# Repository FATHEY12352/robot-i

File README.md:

<div align="center">

<!-- Replace the image path below with your actual product photo in assets/hero_arm.png -->

# 🦾 Robot-i | SO-101 Embodied AI Robotic Arm

**Commercial-Grade, Plug-and-Play 6-DOF Imitation Learning Manipulator & Desktop Control Suite**

[Overview](#-overview) • [Live Demo](#-autonomous-ai-in-action) • [Hardware Specs](#-hardware-specifications) • [Quick Start](#-out-of-the-box-quick-start) • [Architecture](#-system-architecture) • [Versions](#-repository-structure)

</div>

---

## 🌟 Overview

The **Robot-i SO-101** is a complete, ready-to-deploy **6-DOF Embodied AI Robotic Arm** engineered for research labs, industrial automation prototyping, universities, and robotics developers.

Instead of writing rigid, hardcoded inverse-kinematics scripts for every single object position, the **Robot-i SO-101** learns directly from human demonstrations using **Action Chunking with Transformers (ACT)** and dual-camera real-time computer vision.

To ensure a zero-friction experience out of the box, every unit ships with **SO-101 Studio V4**—our standalone desktop software suite that automates environment installation, USB port/camera discovery, calibration, dataset recording, neural network training, and **60 Hz smooth autonomous execution** with a single click.

---

## 🎥 Autonomous AI in Action

<div align="center">

<!-- Replace assets/demo_pick_place.gif with a GIF converted from your test video -->

*Autonomous Pick-and-Place powered by an ACT visuo-motor policy trained on 50 human demonstrations — adapting dynamically to varying object orientations in real time.*

</div>

---

## ⚙️ Hardware Specifications

| Subsystem | Specification | Details |
| :--- | :--- | :--- |
| **Degrees of Freedom** | **6-DOF + Gripper** | Base, Shoulder, Elbow, Wrist Pitch, Wrist Roll, and Precision Parallel Gripper |
| **Actuators** | **Feetech STS3215** | Smart serial bus servos (`1,000,000 baud`) with real-time position, load & voltage feedback |
| **Vision System** | **Dual RGB Cameras** | Overhead Workspace Camera (`top`) + Eye-in-Hand Gripper Camera (`wrist`) @ `640×480, 30 FPS` |
| **Teleoperation** | **Leader-Follower** | 1:1 kinematic Leader arm (supports Servo Bus or ultra-low-latency **ESP32-C3 + AS5600** magnetic encoders) |
| **Control Cadence** | **Up to 60 Hz** | `30 Hz` neural policy inference with `2x` linear trajectory interpolation for jitter-free motion |
| **Compute Support** | **PC & Edge Ready** | Full NVIDIA CUDA (`TF32`) acceleration on Windows/Linux + lightweight deployment on **Raspberry Pi** |
| **Power Supply** | **12V DC** | Regulated 12V power input for high-torque continuous operation |

---

## 🧠 System Architecture

```mermaid
flowchart LR
    subgraph Hardware ["1. Physical Hardware"]
        CAM["📷 Dual RGB Cameras<br/>(Top + Wrist @ 30fps)"]
        FOL["🦾 SO-101 Follower Arm<br/>(STS3215 Bus)"]
        LEA["🎮 Leader Controller<br/>(Teleop Input)"]
    end

    subgraph Studio ["2. SO-101 Studio V4 (Desktop App)"]
        WIZ["🔍 Plug & Play Wizard<br/>(Auto COM & Cam Discovery)"]
        REC["⏺️ Dataset Recorder<br/>(Local Episodes)"]
        TRN["⚡ ACT Policy Trainer<br/>(Local GPU or Cloud ZIP)"]
        ROL["🚀 Autonomous Rollout<br/>(60Hz Smooth Control)"]
    end

    CAM --> WIZ
    FOL --> WIZ
    LEA --> REC
    WIZ --> REC
    REC --> TRN
    TRN --> ROL
    ROL -->|6-Axis Trajectories| FOL
```

---

## 🚀 Out-of-the-Box Quick Start

Setting up your **Robot-i SO-101** on a brand-new Windows PC or Linux / Raspberry Pi machine takes less than 5 minutes—no manual Python or Conda setup required.

### Step 1: Download the Software
Clone this repository (or download and extract the ZIP):
```bash
git clone https://github.com/FATHEY12352/robot-i.git
cd robot-i/v4
```

### Step 2: Launch **SO-101 Studio V4** (1-Click Bootstrap)
* **On Windows:** Double-click **`start_v4.bat`** inside the `v4` folder.
* **On Linux / Raspberry Pi:**
  ```bash
  chmod +x start_v4.sh
  ./start_v4.sh
  ```
> **What happens automatically:** The launcher creates an isolated Python virtual environment (`v4/.venv`), detects your NVIDIA GPU / CUDA or CPU architecture, and opens the **SO-101 Studio V4** graphical interface.

### Step 3: Follow the 5-Tab Workflow Inside the App

<div align="center">
<!-- Replace assets/studio_gui.png with a screenshot of your SO-101 Studio V4 app -->

</div>

1. **Environment & Health Check:** Click **"Install / Repair Full Robotics Environment"** on first run to automatically provision PyTorch and LeRobot.
2. **Hardware & Dual-Cam Wizard:** Choose **Guided Auto-Discovery** (plug in Follower, Leader, Top Camera, and Wrist Camera one by one) and verify both live camera feeds side-by-side.
3. **Record Demonstrations:** Enter your task name (e.g., `"Pick and place"`), set the number of episodes (recommended: `30–50`), and demonstrate the task using the Leader arm.
4. **Train Your AI Policy (ACT):**
   * **Local GPU Training:** Train directly on your workstation with `TF32` acceleration enabled.
   * **Cloud GPU Export:** Click **"Prepare & Compress Dataset for Cloud GPU"** to generate a ready-to-upload `.zip` package for remote RTX 4090 / A100 training, then import the trained checkpoint back in one click.
5. **Autonomous Rollout:** Select your trained model and click **"Start Autonomous Robot"** to watch your SO-101 execute the task independently. Press `Ctrl + C` at any time to safely return the arm to its home pose.

---

## 📂 Repository Structure

| Folder | Description |
| :--- | :--- |
| **`v4/`** | **Current Flagship Release — SO-101 Studio V4** (GUI App, 1-Click Bootstrappers, Hardware Wizard, Cloud Packager & Docs) |
| **`V3/`** | Optimized CLI pipeline with `TF32` ACT training configurations and `60 Hz` rollout benchmarks |
| **`V2/`** | Core LeRobot v0.7.0+ integration, dual-camera calibration, and initial policy inference scripts |
| **`V1/` & `V1 Amazing Hand/`** | Early mechanical prototypes, kinematic studies, and custom end-effector R&D |

---

## 🛠️ Safety & Troubleshooting Tips

* **Emergency Stop & Safe Return:** During autonomous rollout, pressing `Ctrl + C` in the active console smoothly interpolates the arm back to its initial startup position before releasing motor torque.
* **USB Port Re-enumeration:** If you plug the arm into a different USB port on Windows, simply open **Tab 2 (Hardware Wizard)** in Studio V4 and click **Scan Ports** to update your profile in seconds.
* **Magnet & Encoder Alignment (Leader Arm):** If using magnetic rotary encoders (`AS5600`), maintain an air gap of **1.5 mm – 2.0 mm** between the diametrically magnetized magnet and the sensor IC for optimal signal strength.

---

<div align="center">

### 🤝 Built by **Robot-i**

For hardware inquiries, custom gripper designs, or enterprise/lab deployments, open an issue in this repository or contact our engineering team.

</div>

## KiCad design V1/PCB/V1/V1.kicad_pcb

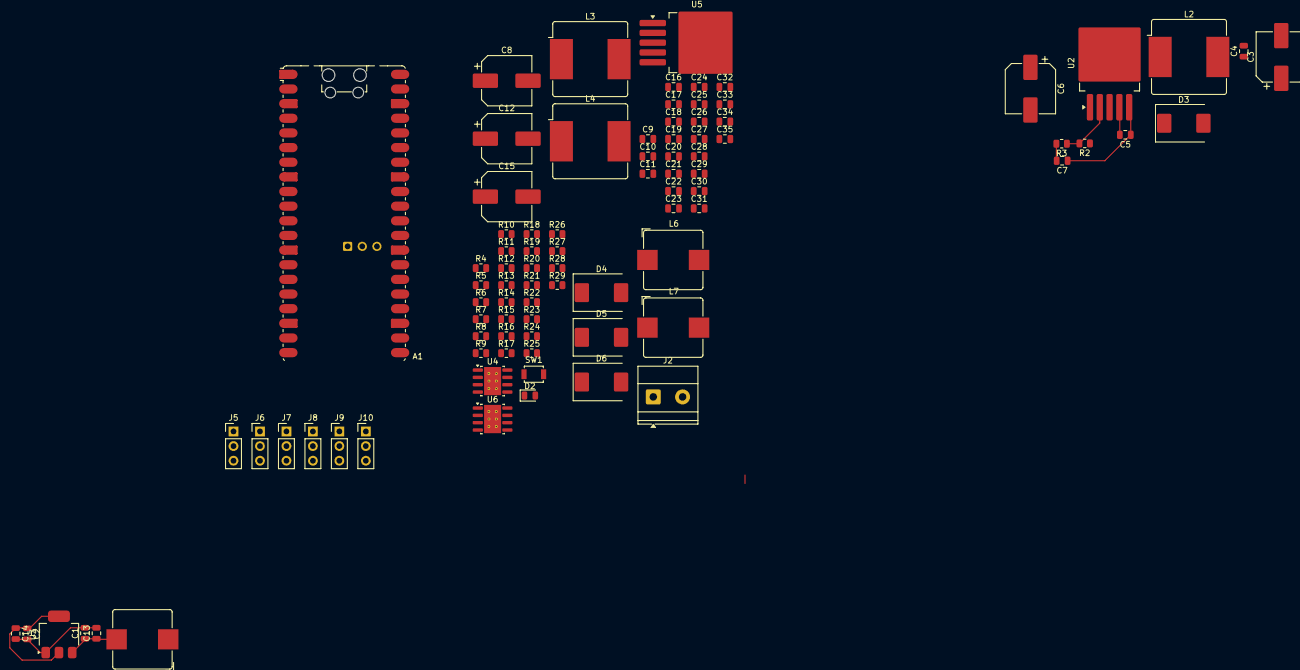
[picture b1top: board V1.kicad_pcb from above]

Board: 2 copper layers, 88 parts (0 on the bottom side), 36 nets.

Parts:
A1: RaspberryPi_Pico_W; RaspberryPi_Pico_W_SMD_HandSolder
C1, C2, C4, C5, C7, C9, C10, C11, C13, C14, C16, C17, C18, C19, C20, C21, C22, C23, C24, C25, C26, C27, C28, C29, C30, C31, C32, C33, C34, C35: C_Small; C_0805_2012Metric
C3, C6, C8, C12, C15: C_Polarized; CP_Elec_8x10.5
D2: LED; LED_0805_2012Metric
D3, D4, D5, D6: D_Schottky; D_SMC
J2: Screw_Terminal_01x02; TerminalBlock_Phoenix_MKDS-1,5-2-5.08_1x02_P5.08mm_Horizont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
J5, J6, J7, J8, J9, J10: Conn_01x04_Pin; PinHeader_1x03_P2.54mm_Vertical
L1, L6, L7: L; L_Bourns_SRP1038C_10.0x10.0mm
L2, L3, L4: L; L_Bourns_SRR1208_12.7x12.7mm
R2, R3, R4, R5, R6, R7, R8, R9, R10, R11, R12, R13, R14, R15, R16, R17, R18, R19, R20, R21, R22, R23, R24, R25, R26, R27, R28, R29: R; R_0805_2012Metric
SW1: SW_DPST_x2; SW_SPST_B3U-1000P
U2, U5: XL4015; TO-263-5_TabPin3
U3: AMS1117-3.3; SOT-223-3_TabPin2
U4, U6: TPS54560BDDA; Texas_R-PDSO-G8_EP2.95x4.9mm_Mask2.4x3.1mm_ThermalVias

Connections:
/F_1: R18.2, R19.1, R20.2, R21.1, R22.2, R23.1, R24.2, R25.1, R26.2, R27.1, R28.2, R29.1
/PWM1: A1.1 (GPIO0), J5.3
/PWM2: A1.2 (GPIO1), J6.3
/PWM3: A1.4 (GPIO2), J7.3
/PWM4: A1.5 (GPIO3), J8.3
/PWM5: A1.6 (GPIO4), J9.3
/PWM6: A1.7 (GPIO5), J10.3
/b+: C5.1, C6.1, C7.1, C8.1, C9.1, C10.1, C15.1, C16.1, C17.1, C18.1, C19.1, C26.1, C27.1, C28.1, C29.1, J2.2, L1.1, L4.1, R9.1, R12.1, U2.5 (VIN), U4.2 (VIN), U5.5 (VIN), U6.2 (VIN)
/s_b: C20.1, C21.1, C22.1, J5.2, J6.2, J7.2, L6.2, R6.1
/s_s: C33.1, C34.1, C35.1, J8.2, J9.2, J10.2, L7.2, R16.1
GND: C1.2, C2.2, C3.2, C4.2, C6.2, C7.2, C8.2, C9.2, C11.2, C12.2, C13.2, C14.2, C15.2, C16.2, C17.2, C18.2, C19.2, C20.2, C21.2, C22.2, C24.2, C25.2, C26.2, C27.2, C28.2, C29.2, C31.2, C32.2, C33.2, C34.2, C35.2, D3.2 (A), D4.2 (A), D5.2 (A), D6.2 (A), J2.1, J5.1, J6.1, J7.1, J8.1, J9.1, J10.1, R3.2, R5.2, R7.2, R8.2, R10.2, R13.2, R14.2, R17.2, R19.2, R21.2, R23.2, R25.2, R27.2, R29.2, U2.1 (GND), U3.1 (GND), U4.7 (GND), U4.9 (GND), U5.1 (GND), U6.7 (GND), U6.9 (GND)
unnamed: A1.3 (GND), A1.8 (GND), A1.13 (GND), A1.18 (GND), A1.23 (GND), A1.28 (GND), A1.38 (GND)
unnamed: C3.1, C4.1, L2.2, R2.1
unnamed: C11.1, C12.1, L3.2, R4.1
unnamed: C25.1, R11.2
unnamed: C31.1, R15.2
unnamed: D3.1 (K), L2.1, U2.3 (SW)
unnamed: D4.1 (K), L3.1, U5.3 (SW)
unnamed: C23.2, D5.1 (K), L6.1, U4.8 (SW)
unnamed: C30.2, D6.1 (K), L7.1, U6.8 (SW)
unnamed: R2.2, R3.1, U2.2 (FB)
unnamed: C5.2, U2.4 (VC)
unnamed: C1.1, C13.1, L1.2, L4.2, U3.3 (VI)
unnamed: C2.1, C14.1, U3.2 (VO)
unnamed: C23.1, U4.1 (BOOT)
unnamed: C24.1, R11.1, U4.6 (COMP)
unnamed: R8.1, R9.2, U4.3 (EN)
unnamed: R6.2, R7.1, U4.5 (FB)
unnamed: R10.1, U4.4 (RT/CLK)
unnamed: R4.2, R5.1, U5.2 (FB)
unnamed: C10.2, U5.4 (VC)
unnamed: C30.1, U6.1 (BOOT)
unnamed: C32.1, R15.1, U6.6 (COMP)
unnamed: R12.2, R13.1, U6.3 (EN)
unnamed: R16.2, R17.1, U6.5 (FB)
unnamed: R14.1, U6.4 (RT/CLK)

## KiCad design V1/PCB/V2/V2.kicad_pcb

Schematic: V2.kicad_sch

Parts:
A1: RaspberryPi_Pico_W; RaspberryPi_Pico_W_SMD_HandSolder
C1, C14: 10uf; C_0805_2012Metric
C2, C7, C9, C13, C23: 100nf; C_0805_2012Metric
C3: C_Polarized; CP_Elec_10x10.5
C4, C5, C6, C19: 2.2uf; C_1210_3225Metric_Pad1.33x2.70mm_HandSolder
C8: C_Polarized; CP_Elec_6.3x5.4
C20, C21, C22: 47uf; C_1210_3225Metric_Pad1.33x2.70mm_HandSolder
C24: 47pf; C_0805_2012Metric
C25: 4700pf; C_0805_2012Metric
D1, D5: D_Schottky; D_SMC
J1, J3, J5, J6, J7, J8, J9, J10: Conn_01x04_Pin; PinHeader_1x04_P1.00mm_Vertical
J2: Screw_Terminal_01x02; TerminalBlock_Phoenix_MKDS-1,5-2-5.08_1x02_P5.08mm_Horizont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
L1: 4.7uf; L_Bourns_SRP1038C_10.0x10.0mm
L6: 7.2uf; L_Bourns_SRP1038C_10.0x10.0mm
R1: 442k; R_0805_2012Metric
R2, R3, R4, R5, R9, R18, R19, R20, R21, R22, R23, R24, R25, R26, R27, R28, R29: 5k; R_0805_2012Metric
R6: 53.6k; R_0805_2012Metric
R7: 10.2k; R_0805_2012Metric
R8: 90.9k; R_0805_2012Metric
R10: 243k; R_0805_2012Metric
R11: 16.9k; R_0805_2012Metric
U1: CD74HC4067SM; SSOP-24_5.3x8.2mm_P0.65mm
U3: AMS1117-3.3; SOT-223-3_TabPin2
U4: TPS54560BDDA; Texas_R-PDSO-G8_EP2.95x4.9mm_Mask2.4x3.1mm_ThermalVias

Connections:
/F_1: R24.2, R25.1, U1.9 (I0)
/F_2: R18.2, R19.1, U1.8 (I1)
/F_3: R26.2, R27.1, U1.7 (I2)
/F_4: R20.2, R21.1, U1.6 (I3)
/F_5: R28.2, R29.1, U1.5 (I4)
/F_6: R22.2, R23.1, U1.4 (I5)
/F_7: R2.2, R3.1, U1.3 (I6)
/F_8: R4.2, R5.1, U1.2 (I7)
/PWM1: A1.10 (GPIO7), J8.3
/PWM2: A1.9 (GPIO6), J5.3
/PWM3: A1.7 (GPIO5), J9.3
/PWM4: A1.6 (GPIO4), J6.3
/PWM5: A1.5 (GPIO3), J10.3
/PWM6: A1.4 (GPIO2), J7.3
/PWM7: A1.2 (GPIO1), J1.3
/PWM8: A1.1 (GPIO0), J3.3
/b+: C3.1, C4.1, C5.1, C6.1, C8.1, C9.1, C19.1, D1.2 (A), L1.1, R1.1, U4.2 (VIN)
/mcu+: A1.37 (3V3_EN), C2.1, C7.1, C14.1, U1.24 (VCC), U3.2 (VO)
/s0: A1.11 (GPIO8), U1.10 (S0)
/s1: A1.12 (GPIO9), U1.11 (S1)
/s2: A1.14 (GPIO10), U1.14 (S2)
/s3: A1.15 (GPIO11), U1.13 (S3)
/s_b: C20.1, C21.1, C22.1, J1.2, J3.2, J5.2, J6.2, J7.2, J8.2, J9.2, J10.2, L6.2, R6.1
/sig: A1.31 (GPIO26_ADC0), U1.1 (COM)
GND: A1.3 (GND), A1.8 (GND), A1.13 (GND), A1.18 (GND), A1.23 (GND), A1.28 (GND), A1.38 (GND), C1.2, C2.2, C3.2, C4.2, C5.2, C6.2, C7.2, C8.2, C9.2, C13.2, C14.2, C19.2, C20.2, C21.2, C22.2, C24.2, C25.2, D5.2 (A), J1.1, J2.1, J3.1, J5.1, J6.1, J7.1, J8.1, J9.1, J10.1, R3.2, R5.2, R7.2, R8.2, R9.1, R10.2, R19.2, R21.2, R23.2, R25.2, R27.2, R29.2, U1.12 (GND), U3.1 (GND), U4.7 (GND), U4.9 (GND)
unnamed: C25.1, R11.2
unnamed: D1.1 (K), J2.2
unnamed: C23.2, D5.1 (K), L6.1, U4.8 (SW)
unnamed: J1.4, R2.1
unnamed: J3.4, R4.1
unnamed: J5.4, R18.1
unnamed: J6.4, R20.1
unnamed: J7.4, R22.1
unnamed: J8.4, R24.1
unnamed: J9.4, R26.1
unnamed: J10.4, R28.1
unnamed: R9.2, U1.15 (~E)
unnamed: C1.1, C13.1, L1.2, U3.3 (VI)
unnamed: C23.1, U4.1 (BOOT)
unnamed: C24.1, R11.1, U4.6 (COMP)
unnamed: R1.2, R8.1, U4.3 (EN)
unnamed: R6.2, R7.1, U4.5 (FB)
unnamed: R10.1, U4.4 (RT/CLK)

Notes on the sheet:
mcu power 3.3
power in
servo con

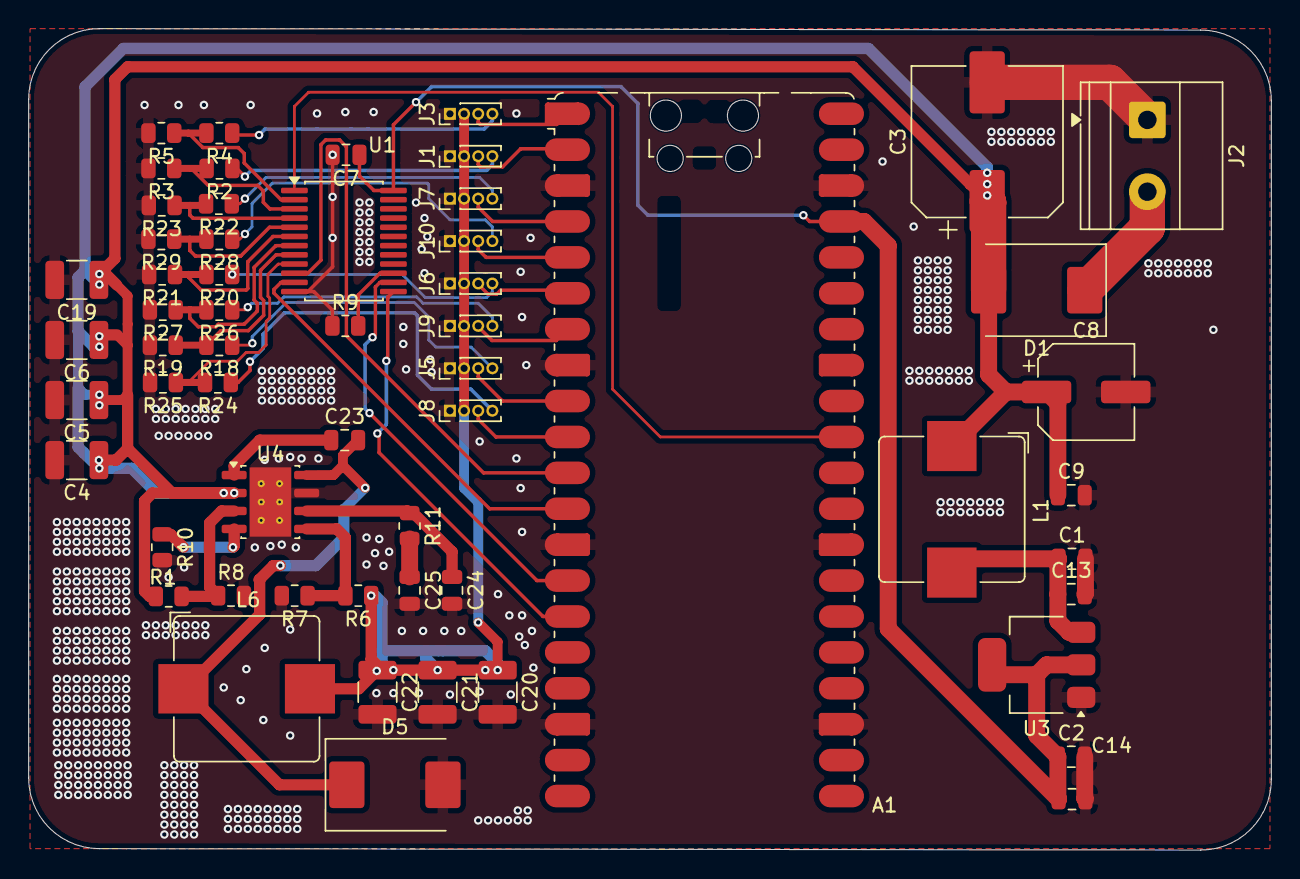
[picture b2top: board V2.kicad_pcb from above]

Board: 2 copper layers, 87.9 x 58.1 mm, 58 parts (0 on the bottom side), 43 nets.

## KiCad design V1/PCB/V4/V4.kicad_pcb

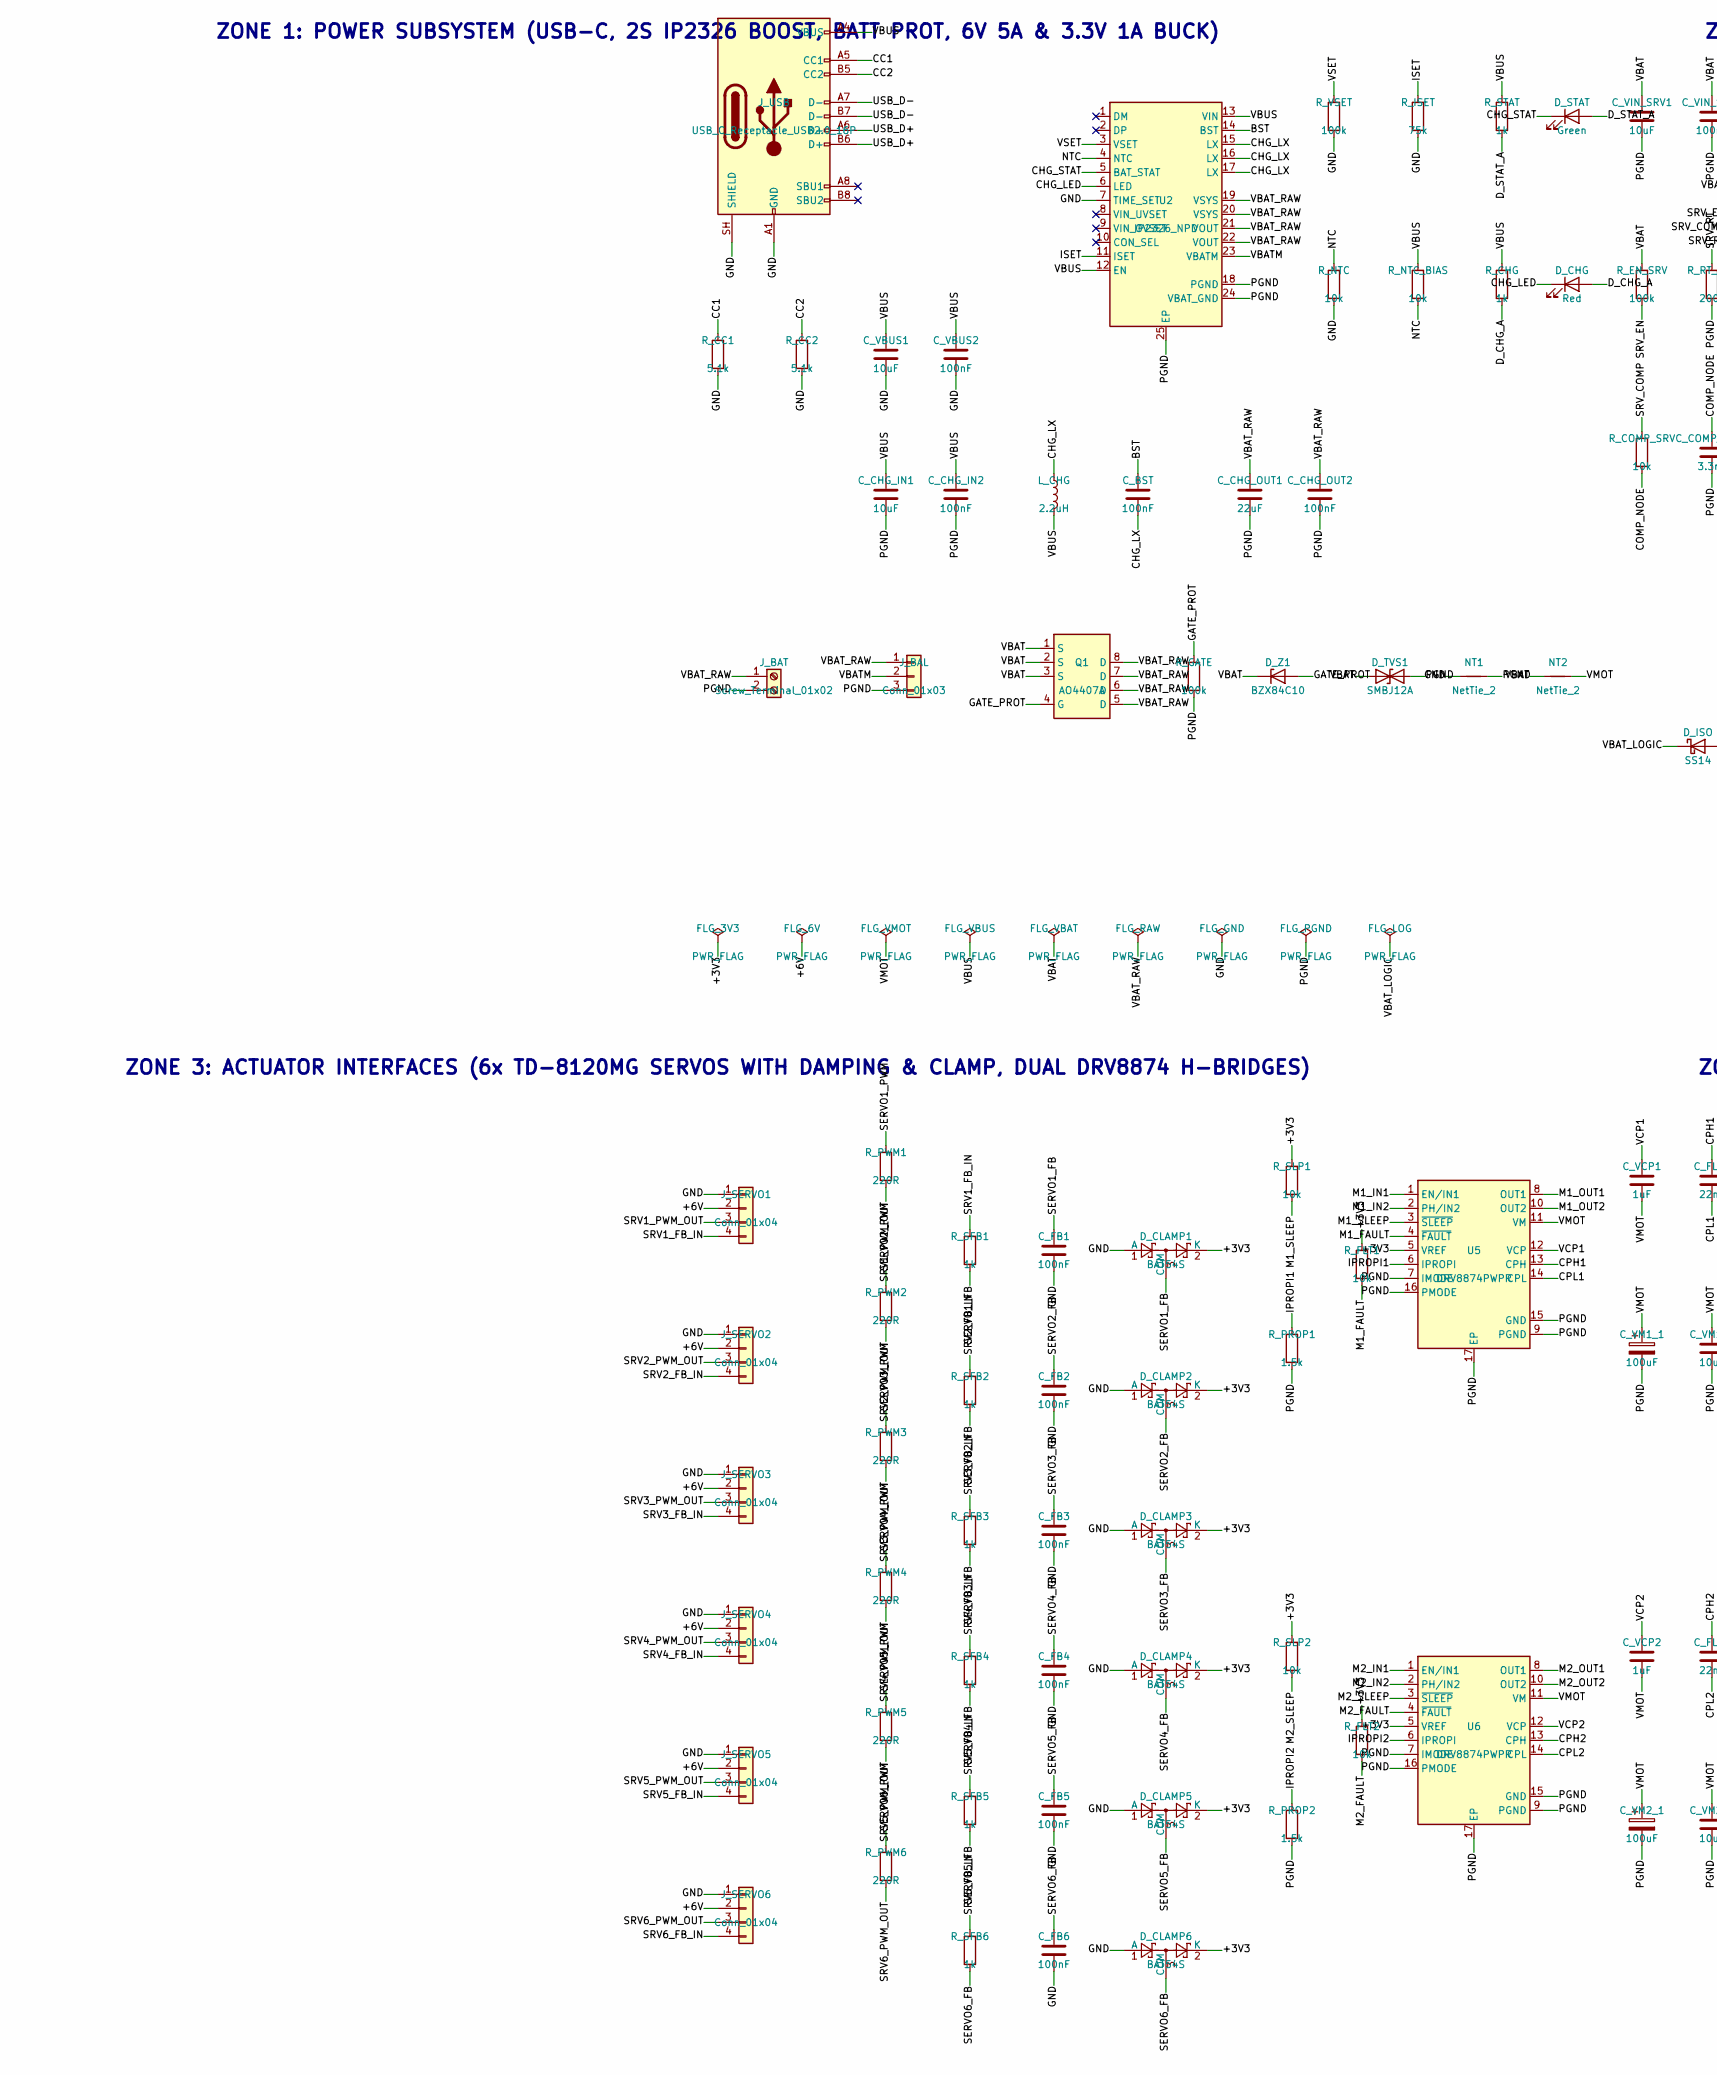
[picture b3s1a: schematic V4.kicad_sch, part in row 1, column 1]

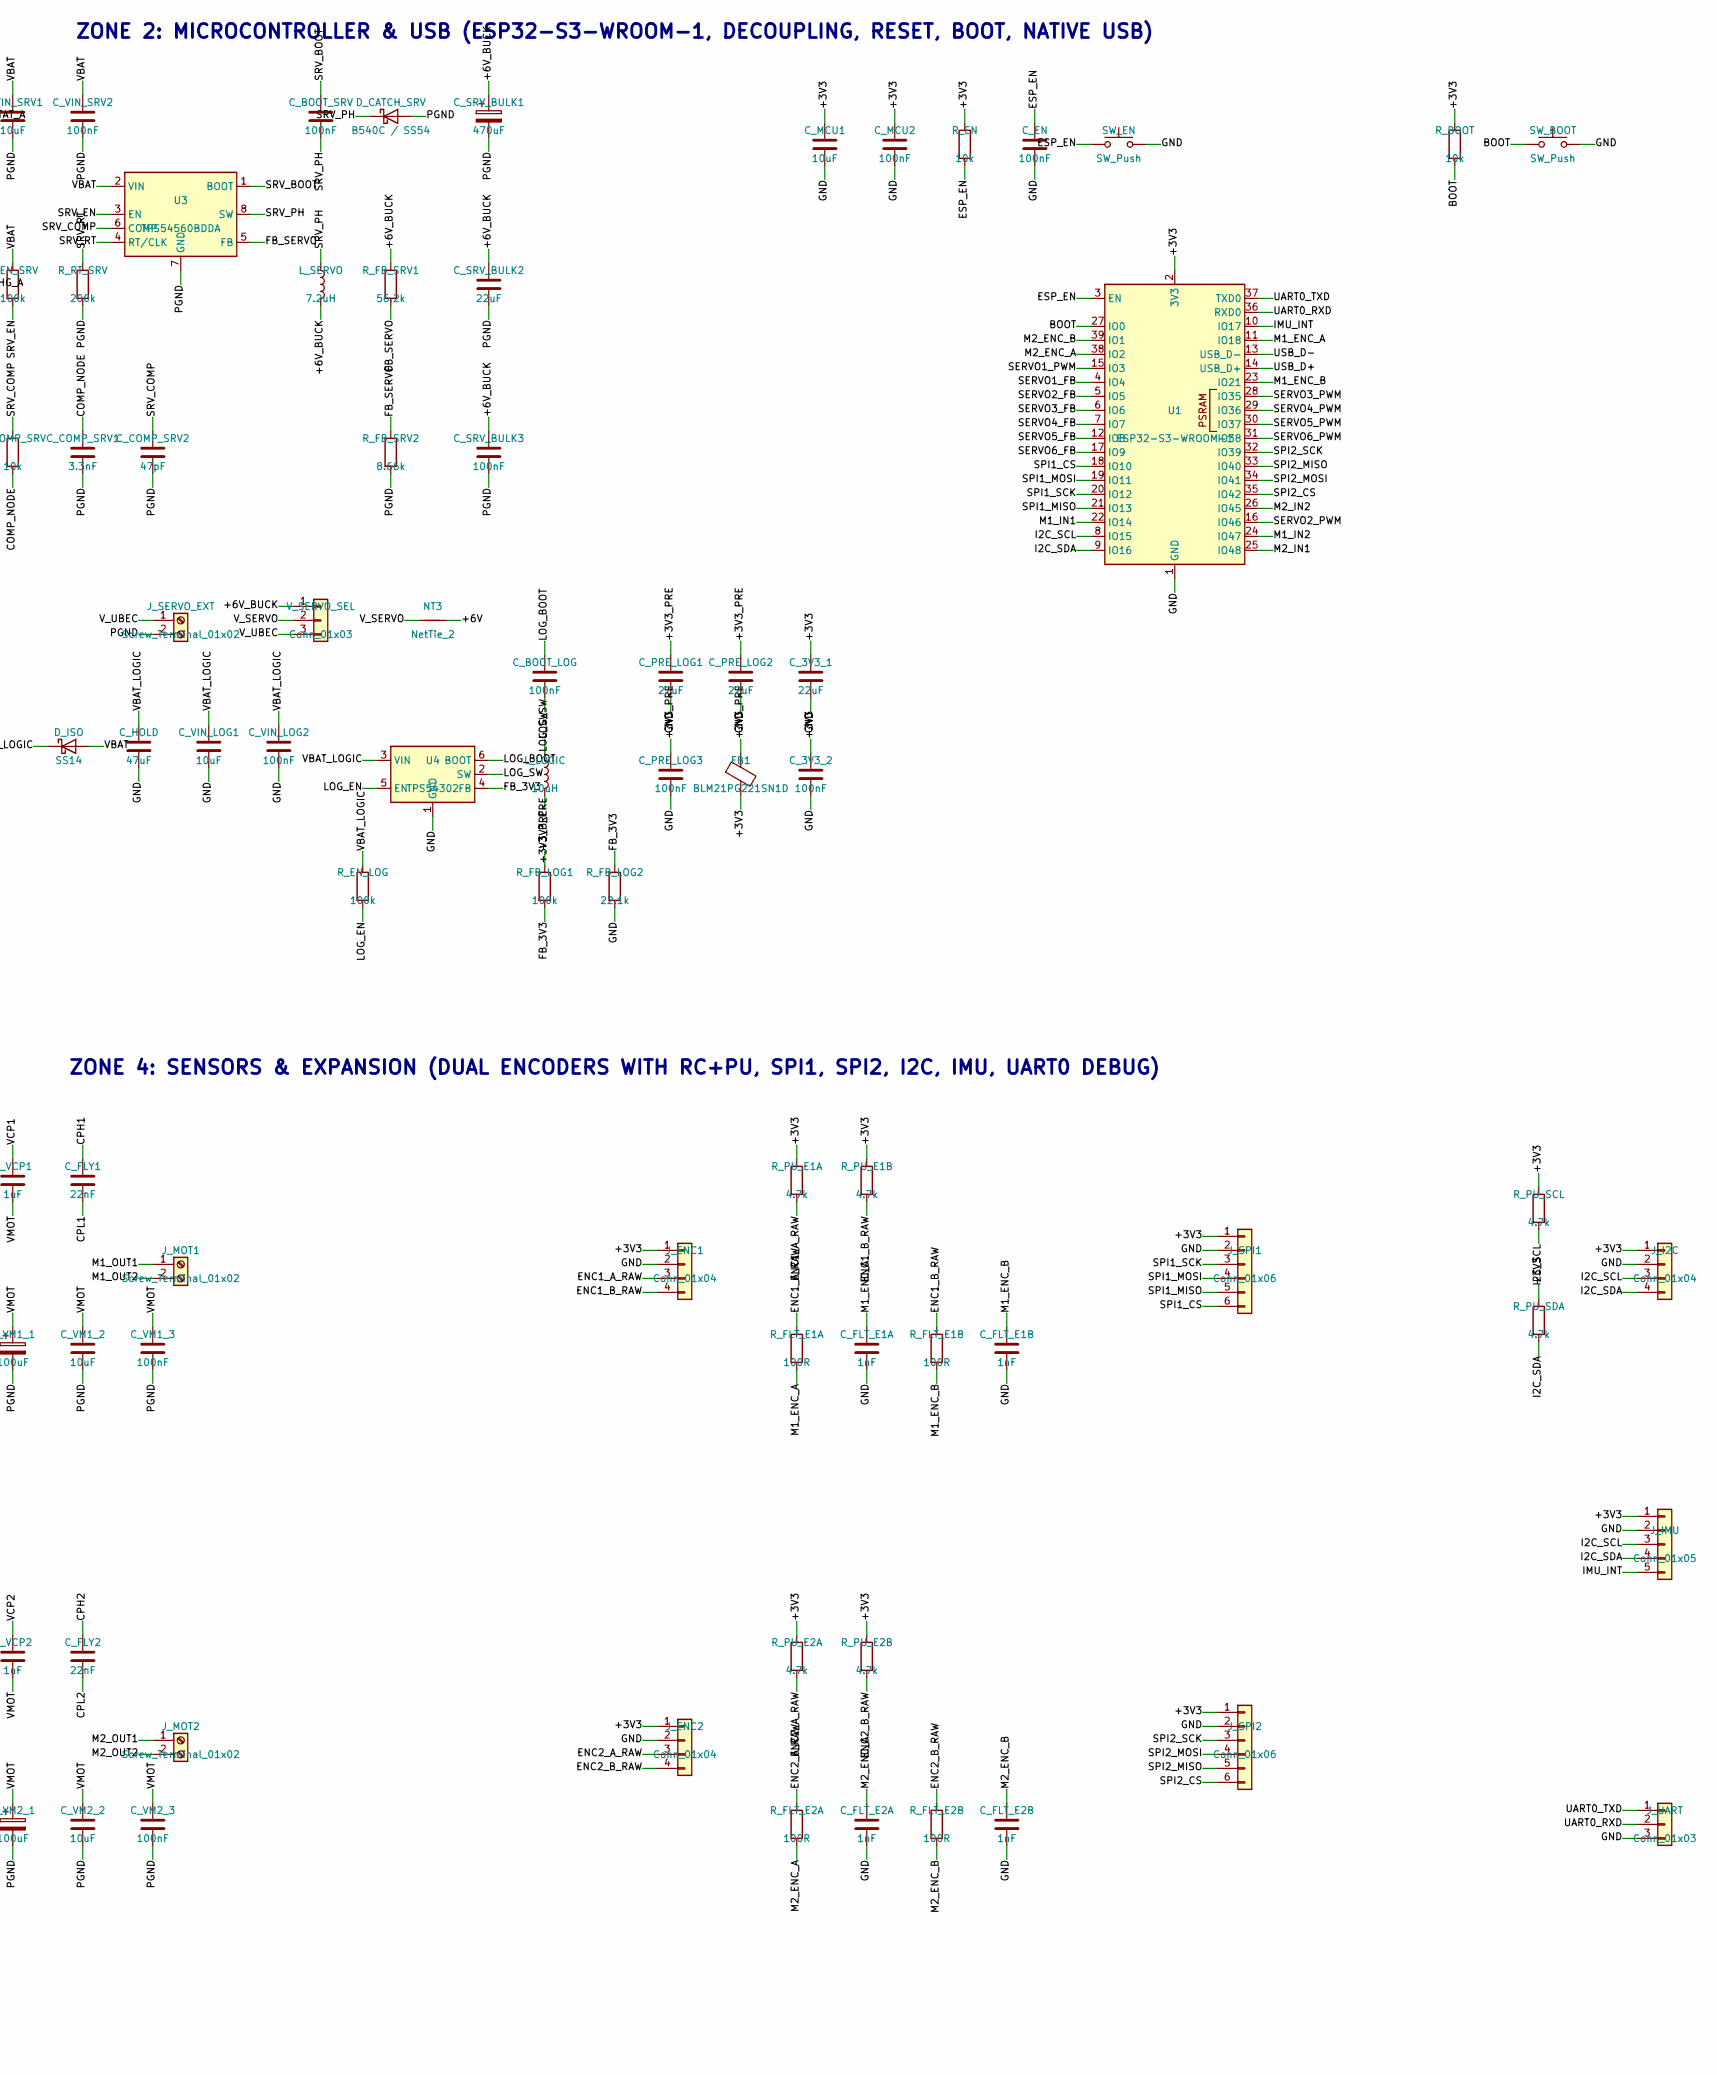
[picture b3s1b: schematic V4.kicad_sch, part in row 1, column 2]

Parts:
C_3V3_1: 22uF; C_0805_2012Metric
C_3V3_2: 100nF; C_0603_1608Metric
C_BOOT_LOG: 100nF; C_0603_1608Metric
C_BOOT_SRV: 100nF; C_0603_1608Metric
C_BST: 100nF; C_0603_1608Metric
C_CHG_IN1: 10uF; C_0805_2012Metric
C_CHG_IN2: 100nF; C_0603_1608Metric
C_CHG_OUT1: 22uF; C_0805_2012Metric
C_CHG_OUT2: 100nF; C_0603_1608Metric
C_COMP_SRV1: 3.3nF; C_0603_1608Metric
C_COMP_SRV2: 47pF; C_0603_1608Metric
C_EN: 100nF; C_0603_1608Metric
C_FB1, C_FB2, C_FB3, C_FB4, C_FB5, C_FB6: 100nF; C_0603_1608Metric
C_FLT_E1A, C_FLT_E1B, C_FLT_E2A, C_FLT_E2B: 1nF; C_0603_1608Metric
C_FLY1, C_FLY2: 22nF; C_0603_1608Metric
C_HOLD: 47uF; C_1206_3216Metric
C_MCU1: 10uF; C_0805_2012Metric
C_MCU2: 100nF; C_0603_1608Metric
C_PRE_LOG1, C_PRE_LOG2: 22uF; C_0805_2012Metric
C_PRE_LOG3: 100nF; C_0603_1608Metric
C_SRV_BULK1: 470uF; CP_Elec_8x10.5
C_SRV_BULK2: 22uF; C_1206_3216Metric
C_SRV_BULK3: 100nF; C_0603_1608Metric
C_VBUS1: 10uF; C_0805_2012Metric
C_VBUS2: 100nF; C_0603_1608Metric
C_VCP1, C_VCP2: 1uF; C_0603_1608Metric
C_VIN_LOG1: 10uF; C_0805_2012Metric
C_VIN_LOG2: 100nF; C_0603_1608Metric
C_VIN_SRV1: 10uF; C_1206_3216Metric
C_VIN_SRV2: 100nF; C_0603_1608Metric
C_VM1_1, C_VM2_1: 100uF; CP_Elec_6.3x5.4
C_VM1_2, C_VM2_2: 10uF; C_0805_2012Metric
C_VM1_3, C_VM2_3: 100nF; C_0603_1608Metric
D_CATCH_SRV: B540C / SS54; D_SMC
D_CHG: Red; LED_0805_2012Metric
D_CLAMP1, D_CLAMP2, D_CLAMP3, D_CLAMP4, D_CLAMP5, D_CLAMP6: BAT54S; SOT-23
D_ISO: SS14; D_SMA
D_STAT: Green; LED_0805_2012Metric
D_TVS1: SMBJ12A; D_SMB
D_Z1: BZX84C10; D_SOD-323
FB1: BLM21PG221SN1D; L_0805_2012Metric
FLG_3V3, FLG_6V: PWR_FLAG
FLG_GND: PWR_FLAG
FLG_LOG: PWR_FLAG
FLG_PGND: PWR_FLAG
FLG_RAW: PWR_FLAG
FLG_VBAT: PWR_FLAG
FLG_VBUS: PWR_FLAG
FLG_VMOT: PWR_FLAG
J_BAL: Conn_01x03; JST_XH_B3B-XH-A_1x03_P2.50mm_Vertical
J_BAT: Screw_Terminal_01x02; TerminalBlock_Phoenix_MKDS-1,5-2-5.08_1x02_P5.08mm_Horizont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
J_ENC1, J_ENC2: Conn_01x04; PinHeader_1x04_P2.54mm_Vertical
J_I2C: Conn_01x04; PinHeader_1x04_P2.54mm_Vertical
J_IMU: Conn_01x05; PinHeader_1x05_P2.54mm_Vertical
J_MOT1, J_MOT2: Screw_Terminal_01x02; TerminalBlock_Phoenix_MKDS-1,5-2-5.08_1x02_P5.08mm_Horizont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
J_SERVO1, J_SERVO2, J_SERVO3, J_SERVO4, J_SERVO5, J_SERVO6: Conn_01x04; PinHeader_1x04_P2.54mm_Vertical
J_SERVO_EXT: Screw_Terminal_01x02; TerminalBlock_Phoenix_MKDS-1,5-2-5.08_1x02_P5.08mm_Horizont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
J_SPI1, J_SPI2: Conn_01x06; PinHeader_1x06_P2.54mm_Vertical
J_UART: Conn_01x03; PinHeader_1x03_P2.54mm_Vertical
J_USB: USB_C_Receptacle_USB2.0_16P; USB_C_Receptacle_HRO_TYPE-C-31-M-12
L_CHG: 2.2uH; L_Bourns_SRP7028A_7.3x6.6mm
L_LOGIC: 10uH; L_Bourns_SRP5030T
L_SERVO: 7.2uH; L_Bourns_SRP1038C_10.0x10.0mm
NT1, NT2, NT3: NetTie_2; NetTie-2_SMD_Pad0.5mm
Q1: AO4407A; SOIC-8_3.9x4.9mm_P1.27mm
R_BOOT: 10k; R_0603_1608Metric
R_CC1, R_CC2: 5.1k; R_0603_1608Metric
R_CHG: 1k; R_0603_1608Metric
R_COMP_SRV: 10k; R_0603_1608Metric
R_EN: 10k; R_0603_1608Metric
R_EN_LOG: 100k; R_0603_1608Metric
R_EN_SRV: 100k; R_0603_1608Metric
R_FB_LOG1: 100k; R_0603_1608Metric
R_FB_LOG2: 22.1k; R_0603_1608Metric
R_FB_SRV1: 56.2k; R_0603_1608Metric
R_FB_SRV2: 8.66k; R_0603_1608Metric
R_FLT1, R_FLT2: 10k; R_0603_1608Metric
R_FLT_E1A, R_FLT_E1B, R_FLT_E2A, R_FLT_E2B: 100R; R_0603_1608Metric
R_GATE: 100k; R_0603_1608Metric
R_ISET: 75k; R_0603_1608Metric
R_NTC: 10k; R_0603_1608Metric
R_NTC_BIAS: 10k; R_0603_1608Metric
R_PROP1, R_PROP2: 1.5k; R_0603_1608Metric
R_PU_E1A, R_PU_E1B, R_PU_E2A, R_PU_E2B: 4.7k; R_0603_1608Metric
R_PU_SCL: 4.7k; R_0603_1608Metric
R_PU_SDA: 4.7k; R_0603_1608Metric
R_PWM1, R_PWM2, R_PWM3, R_PWM4, R_PWM5, R_PWM6: 220R; R_0603_1608Metric
R_RT_SRV: 200k; R_0603_1608Metric
R_SFB1, R_SFB2, R_SFB3, R_SFB4, R_SFB5, R_SFB6: 1k; R_0603_1608Metric
R_SLP1, R_SLP2: 10k; R_0603_1608Metric
R_STAT: 1k; R_0603_1608Metric
R_VSET: 100k; R_0603_1608Metric
SW_BOOT: SW_Push; SW_Push_1P1T_NO_CK_KMR2
SW_EN: SW_Push; SW_Push_1P1T_NO_CK_KMR2
U1: ESP32-S3-WROOM-1
U2: IP2326_NPD; QFN-24-1EP_4x4mm_P0.5mm_EP2.7x2.7mm
U3: TPS54560BDDA; SOIC-8-1EP_3.9x4.9mm_P1.27mm_EP2.95x4.9mm_Mask2.71x3.4mm_Th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
U4: TPS54302; SOT-23-6
U5, U6: DRV8874PWPR; HTSSOP-16-1EP_4.4x5mm_P0.65mm_EP3.4x5mm_Mask2.46x2.31mm_The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
V_SERVO_SEL: Conn_01x03; PinHeader_1x03_P2.54mm_Vertical

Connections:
+3V3: C_3V3_1.1, C_3V3_2.1, C_MCU1.1, C_MCU2.1, D_CLAMP1.2 (K), D_CLAMP2.2 (K), D_CLAMP3.2 (K), D_CLAMP4.2 (K), D_CLAMP5.2 (K), D_CLAMP6.2 (K), FB1.2, FLG_3V3.1, J_ENC1.1, J_ENC2.1, J_I2C.1, J_IMU.1, J_SPI1.1, J_SPI2.1, R_BOOT.1, R_EN.1, R_FLT1.1, R_FLT2.1, R_PU_E1A.1, R_PU_E1B.1, R_PU_E2A.1, R_PU_E2B.1, R_PU_SCL.1, R_PU_SDA.1, R_SLP1.1, R_SLP2.1, U1.2 (3V3), U5.5 (VREF), U6.5 (VREF)
+3V3_PRE: C_PRE_LOG1.1, C_PRE_LOG2.1, C_PRE_LOG3.1, FB1.1, L_LOGIC.2, R_FB_LOG1.1
+6V: FLG_6V.1, J_SERVO1.2, J_SERVO2.2, J_SERVO3.2, J_SERVO4.2, J_SERVO5.2, J_SERVO6.2, NT3.2
+6V_BUCK: C_SRV_BULK1.1, C_SRV_BULK2.1, C_SRV_BULK3.1, L_SERVO.2, R_FB_SRV1.1, V_SERVO_SEL.1
BOOT: R_BOOT.2, SW_BOOT.1, U1.27 (IO0)
BST: C_BST.1, U2.14 (BST)
CC1: J_USB.A5 (CC1), R_CC1.1
CC2: J_USB.B5 (CC2), R_CC2.1
CHG_LED: D_CHG.1 (K), U2.6 (LED)
CHG_LX: C_BST.2, L_CHG.1, U2.1 (DM), U2.2 (DP), U2.8 (VIN_UVSET), U2.9 (VIN_OVSET), U2.10 (CON_SEL), U2.15 (LX), U2.16 (LX), U2.17 (LX)
CHG_STAT: D_STAT.1 (K), U2.5 (BAT_STAT)
COMP_NODE: C_COMP_SRV1.1, R_COMP_SRV.2
CPH1: C_FLY1.1, U5.13 (CPH)
CPH2: C_FLY2.1, U6.13 (CPH)
CPL1: C_FLY1.2, U5.14 (CPL)
CPL2: C_FLY2.2, U6.14 (CPL)
D_CHG_A: D_CHG.2 (A), R_CHG.2
D_STAT_A: D_STAT.2 (A), R_STAT.2
ENC1_A_RAW: J_ENC1.3, R_FLT_E1A.1, R_PU_E1A.2
ENC1_B_RAW: J_ENC1.4, R_FLT_E1B.1, R_PU_E1B.2
ENC2_A_RAW: J_ENC2.3, R_FLT_E2A.1, R_PU_E2A.2
ENC2_B_RAW: J_ENC2.4, R_FLT_E2B.1, R_PU_E2B.2
ESP_EN: C_EN.1, R_EN.2, SW_EN.1, U1.3 (EN)
FB_3V3: R_FB_LOG1.2, R_FB_LOG2.1, U4.4 (FB)
FB_SERVO: R_FB_SRV1.2, R_FB_SRV2.1, U3.5 (FB)
GATE_PROT: D_Z1.2 (A), Q1.4 (G), R_GATE.1
GND: C_3V3_1.2, C_3V3_2.2, C_EN.2, C_FB1.2, C_FB2.2, C_FB3.2, C_FB4.2, C_FB5.2, C_FB6.2, C_FLT_E1A.2, C_FLT_E1B.2, C_FLT_E2A.2, C_FLT_E2B.2, C_HOLD.2, C_MCU1.2, C_MCU2.2, C_PRE_LOG1.2, C_PRE_LOG2.2, C_PRE_LOG3.2, C_VBUS1.2, C_VBUS2.2, C_VIN_LOG1.2, C_VIN_LOG2.2, D_CLAMP1.1 (A), D_CLAMP2.1 (A), D_CLAMP3.1 (A), D_CLAMP4.1 (A), D_CLAMP5.1 (A), D_CLAMP6.1 (A), FLG_GND.1, J_ENC1.2, J_ENC2.2, J_I2C.2, J_IMU.2, J_SERVO1.1, J_SERVO2.1, J_SERVO3.1, J_SERVO4.1, J_SERVO5.1, J_SERVO6.1, J_SPI1.2, J_SPI2.2, J_UART.3, J_USB.A1 (GND), J_USB.A12 (GND), J_USB.B1 (GND), J_USB.B12 (GND), J_USB.SH (SHIELD), NT1.1, R_CC1.2, R_CC2.2, R_FB_LOG2.2, R_ISET.2, R_NTC.2, R_VSET.2, SW_BOOT.2, SW_EN.2, U1.1 (GND), U1.40 (GND), U1.41 (GND), U2.7 (TIME_SET), U4.1 (GND); also elsewhere on the board
I2C_SCL: J_I2C.3, J_IMU.3, R_PU_SCL.2, U1.8 (IO15)
I2C_SDA: J_I2C.4, J_IMU.4, R_PU_SDA.2, U1.9 (IO16)
IMU_INT: J_IMU.5, U1.10 (IO17)
IPROPI1: R_PROP1.1, U5.6 (IPROPI)
IPROPI2: R_PROP2.1, U6.6 (IPROPI)
ISET: R_ISET.1, U2.11 (ISET)
LOG_BOOT: C_BOOT_LOG.1, U4.6 (BOOT)
LOG_EN: R_EN_LOG.2, U4.5 (EN)
LOG_SW: C_BOOT_LOG.2, L_LOGIC.1, U4.2 (SW)
M1_ENC_A: C_FLT_E1A.1, R_FLT_E1A.2, U1.11 (IO18)
M1_ENC_B: C_FLT_E1B.1, R_FLT_E1B.2, U1.23 (IO21)
M1_FAULT: R_FLT1.2, U5.4 (~FAULT)
M1_IN1: U1.22 (IO14), U5.1 (EN/IN1)
M1_IN2: U1.24 (IO47), U5.2 (PH/IN2)
M1_OUT1: J_MOT1.1, U5.8 (OUT1)
M1_OUT2: J_MOT1.2, U5.10 (OUT2)
M1_SLEEP: R_SLP1.2, U5.3 (~SLEEP)
M2_ENC_A: C_FLT_E2A.1, R_FLT_E2A.2, U1.38 (IO2)
M2_ENC_B: C_FLT_E2B.1, R_FLT_E2B.2, U1.39 (IO1)
M2_FAULT: R_FLT2.2, U6.4 (~FAULT)
M2_IN1: U1.25 (IO48), U6.1 (EN/IN1)
M2_IN2: U1.26 (IO45), U6.2 (PH/IN2)
M2_OUT1: J_MOT2.1, U6.8 (OUT1)
M2_OUT2: J_MOT2.2, U6.10 (OUT2)
M2_SLEEP: R_SLP2.2, U6.3 (~SLEEP)
NTC: R_NTC.1, R_NTC_BIAS.2, U2.4 (NTC)
PGND: C_CHG_IN1.2, C_CHG_IN2.2, C_CHG_OUT1.2, C_CHG_OUT2.2, C_COMP_SRV1.2, C_COMP_SRV2.2, C_SRV_BULK1.2, C_SRV_BULK2.2, C_SRV_BULK3.2, C_VIN_SRV1.2, C_VIN_SRV2.2, C_VM1_1.2, C_VM1_2.2, C_VM1_3.2, C_VM2_1.2, C_VM2_2.2, C_VM2_3.2, D_CATCH_SRV.2 (A), D_TVS1.2 (A2), FLG_PGND.1, J_BAL.3, J_BAT.2, J_SERVO_EXT.2, NT1.2, R_FB_SRV2.2, R_GATE.2, R_PROP1.2, R_PROP2.2, R_RT_SRV.2, U2.18 (PGND), U2.24 (VBAT_GND), U2.25 (EP), U3.7 (GND), U3.9 (GND), U5.7 (IMODE), U5.9 (PGND), U5.15 (GND), U5.16 (PMODE), U5.17 (EP), U6.7 (IMODE), U6.9 (PGND), U6.15 (GND), U6.16 (PMODE), U6.17 (EP)
SERVO1_FB: C_FB1.1, D_CLAMP1.3 (COM), R_SFB1.2, U1.4 (IO4)
SERVO1_PWM: R_PWM1.1, U1.15 (IO3)
SERVO2_FB: C_FB2.1, D_CLAMP2.3 (COM), R_SFB2.2, U1.5 (IO5)
SERVO2_PWM: R_PWM2.1, U1.16 (IO46)
SERVO3_FB: C_FB3.1, D_CLAMP3.3 (COM), R_SFB3.2, U1.6 (IO6)
SERVO3_PWM: R_PWM3.1, U1.28 (IO35)
SERVO4_FB: C_FB4.1, D_CLAMP4.3 (COM), R_SFB4.2, U1.7 (IO7)
SERVO4_PWM: R_PWM4.1, U1.29 (IO36)
SERVO5_FB: C_FB5.1, D_CLAMP5.3 (COM), R_SFB5.2, U1.12 (IO8)
SERVO5_PWM: R_PWM5.1, U1.30 (IO37)
SERVO6_FB: C_FB6.1, D_CLAMP6.3 (COM), R_SFB6.2, U1.17 (IO9)
SERVO6_PWM: R_PWM6.1, U1.31 (IO38)
SPI1_CS: J_SPI1.6, U1.18 (IO10)
SPI1_MISO: J_SPI1.5, U1.21 (IO13)
SPI1_MOSI: J_SPI1.4, U1.19 (IO11)
SPI1_SCK: J_SPI1.3, U1.20 (IO12)
SPI2_CS: J_SPI2.6, U1.35 (IO42)
SPI2_MISO: J_SPI2.5, U1.33 (IO40)
SPI2_MOSI: J_SPI2.4, U1.34 (IO41)
SPI2_SCK: J_SPI2.3, U1.32 (IO39)
SRV1_FB_IN: J_SERVO1.4, R_SFB1.1
SRV1_PWM_OUT: J_SERVO1.3, R_PWM1.2
SRV2_FB_IN: J_SERVO2.4, R_SFB2.1
SRV2_PWM_OUT: J_SERVO2.3, R_PWM2.2
SRV3_FB_IN: J_SERVO3.4, R_SFB3.1
SRV3_PWM_OUT: J_SERVO3.3, R_PWM3.2
SRV4_FB_IN: J_SERVO4.4, R_SFB4.1
SRV4_PWM_OUT: J_SERVO4.3, R_PWM4.2
SRV5_FB_IN: J_SERVO5.4, R_SFB5.1
SRV5_PWM_OUT: J_SERVO5.3, R_PWM5.2
SRV6_FB_IN: J_SERVO6.4, R_SFB6.1
SRV6_PWM_OUT: J_SERVO6.3, R_PWM6.2
SRV_BOOT: C_BOOT_SRV.1, U3.1 (BOOT)
SRV_COMP: C_COMP_SRV2.1, R_COMP_SRV.1, U3.6 (COMP)
SRV_EN: R_EN_SRV.2, U3.3 (EN)
SRV_PH: C_BOOT_SRV.2, D_CATCH_SRV.1 (K), L_SERVO.1, U3.8 (SW)
SRV_RT: R_RT_SRV.1, U3.4 (RT/CLK)
UART0_RXD: J_UART.2, U1.36 (RXD0)
UART0_TXD: J_UART.1, U1.37 (TXD0)
USB_D+: J_USB.A6 (D+), J_USB.B6 (D+), U1.14 (USB_D+)
USB_D-: J_USB.A7 (D-), J_USB.B7 (D-), U1.13 (USB_D-)
VBAT: C_VIN_SRV1.1, C_VIN_SRV2.1, D_ISO.2 (A), D_TVS1.1 (A1), D_Z1.1 (K), FLG_VBAT.1, NT2.1, Q1.1 (S), Q1.2 (S), Q1.3 (S), R_EN_SRV.1, U3.2 (VIN)
VBATM: J_BAL.2, U2.23 (VBATM)
VBAT_LOGIC: C_HOLD.1, C_VIN_LOG1.1, C_VIN_LOG2.1, D_ISO.1 (K), FLG_LOG.1, R_EN_LOG.1, U4.3 (VIN)
VBAT_RAW: C_CHG_OUT1.1, C_CHG_OUT2.1, FLG_RAW.1, J_BAL.1, J_BAT.1, Q1.5 (D), Q1.6 (D), Q1.7 (D), Q1.8 (D), U2.19 (VSYS), U2.20 (VSYS), U2.21 (VOUT), U2.22 (VOUT)
VBUS: C_CHG_IN1.1, C_CHG_IN2.1, C_VBUS1.1, C_VBUS2.1, FLG_VBUS.1, J_USB.A4 (VBUS), J_USB.A9 (VBUS), J_USB.B4 (VBUS), J_USB.B9 (VBUS), L_CHG.2, R_CHG.1, R_NTC_BIAS.1, R_STAT.1, U2.12 (EN), U2.13 (VIN)
VCP1: C_VCP1.1, U5.12 (VCP)
VCP2: C_VCP2.1, U6.12 (VCP)
VMOT: C_VCP1.2, C_VCP2.2, C_VM1_1.1, C_VM1_2.1, C_VM1_3.1, C_VM2_1.1, C_VM2_2.1, C_VM2_3.1, FLG_VMOT.1, NT2.2, U5.11 (VM), U6.11 (VM)
VSET: R_VSET.1, U2.3 (VSET)
V_SERVO: NT3.1, V_SERVO_SEL.2
V_UBEC: J_SERVO_EXT.1, V_SERVO_SEL.3

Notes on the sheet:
ZONE 1: POWER SUBSYSTEM (USB-C, 2S IP2326 BOOST, BATT PROT, 6V 5A & 3.3V 1A BUCK)
ZONE 2: MICROCONTROLLER & USB (ESP32-S3-WROOM-1, DECOUPLING, RESET, BOOT, NATIVE USB)
ZONE 3: ACTUATOR INTERFACES (6x TD-8120MG SERVOS WITH DAMPING & CLAMP, DUAL DRV8874 H-BRIDGES)
ZONE 4: SENSORS & EXPANSION (DUAL ENCODERS WITH RC+PU, SPI1, SPI2, I2C, IMU, UART0 DEBUG)

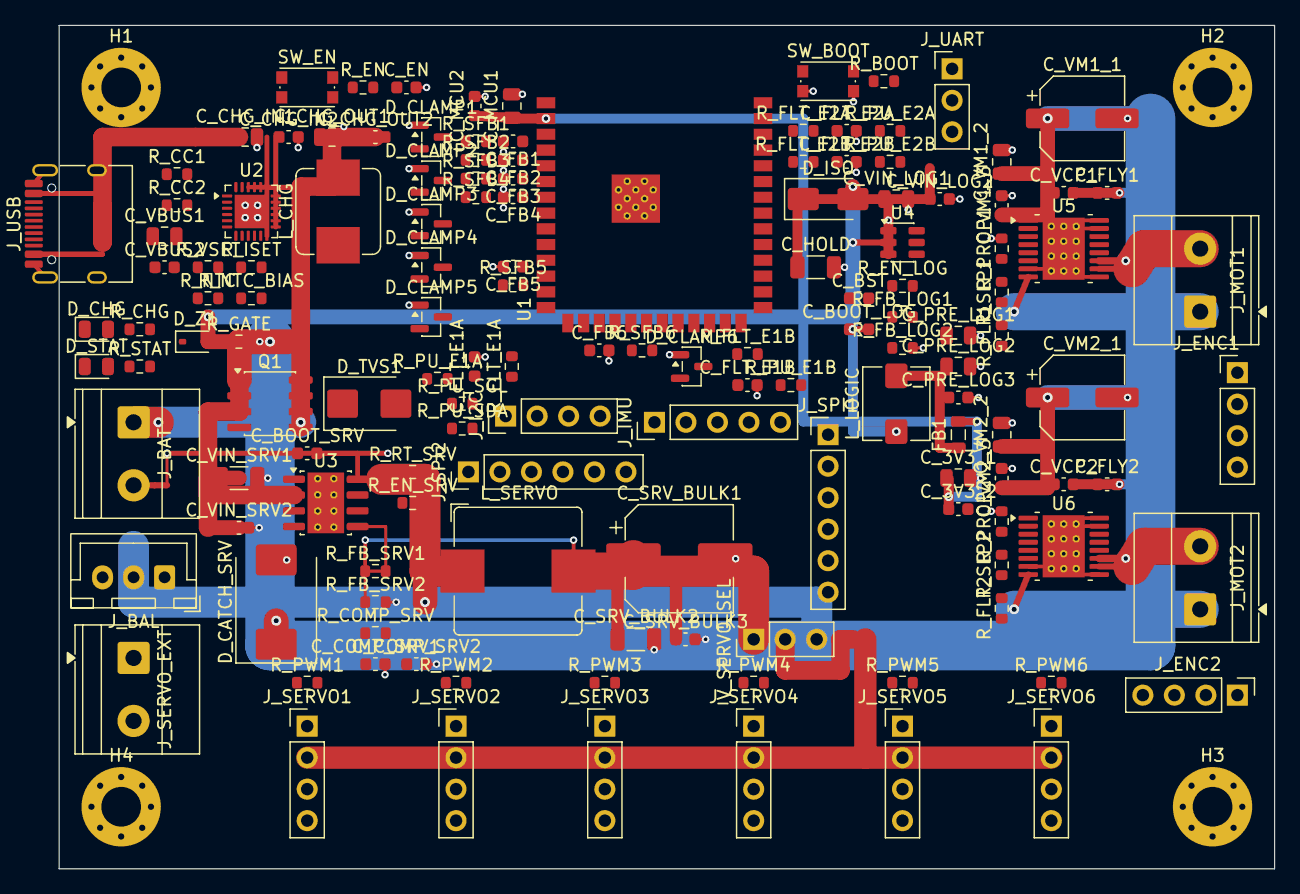
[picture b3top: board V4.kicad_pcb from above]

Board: 2 copper layers, 98.0 x 68.0 mm, 146 parts (0 on the bottom side), 106 nets.

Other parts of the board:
H1, H2, H3, H4: MountingHole_3.2mm_M3_Pad_Via

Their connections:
GND: H1.1, H2.1, H3.1, H4.1; also elsewhere on the board
